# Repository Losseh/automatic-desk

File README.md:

# README

## Used components

### Microcontroller
Arduino Nano 328 SKU DFR0010 (from DFRobot)
[wiki](https://wiki.dfrobot.com/Arduino_Nano_328__SKU__DFR0010_)

### Current sensor
ACS712 5A

### Motor driver
[Cytron MD13S](https://www.cytron.io/p-13amp-6v-30v-dc-motor-driver)

### Motor
JGB37-555

# Troubleshooting

## Arduino-ide

### sandbox issue

```
[18644:1223/101056.126347:FATAL:setuid_sandbox_host.cc(158)] The SUID sandbox helper binary was found, but is not configured correctly. Rather than run without sandboxing I'm aborting now. You need to make sure that /home/justyna-halicz-szymanska/Programy/arduino-ide_2.3.7_Linux_64bit/chrome-sandbox is owned by root and has mode 4755.
Pułapka debuggera/breakpoint (zrzut pamięci)
```

solution
```
sudo chown root chrome-sandbox
sudo chmod g+x,u+s chrome-sandbox
```

### Error: programmer is not responding

trying to upload a program to dfrduino nano 4.0 using android ide. but getting:
```
Sketch uses 924 bytes (3%) of program storage space. Maximum is 30720 bytes.
Global variables use 9 bytes (0%) of dynamic memory, leaving 2039 bytes for local variables. Maximum is 2048 bytes.
Error: programmer is not responding Warning: attempt 1 of 10: not in sync: resp=0x00
Error: programmer is not responding Warning: attempt 2 of 10: not in sync: resp=0x00
Error: programmer is not responding Warning: attempt 3 of 10: not in sync: resp=0x00
...
```

solution
```
Select Arduino Nano
Try ATmega328P
If that doesn't work, try ATmega328P (Old Bootloader)

The Nano 4.0 is based on the ATmega328P, and the bootloader variant matters.
```

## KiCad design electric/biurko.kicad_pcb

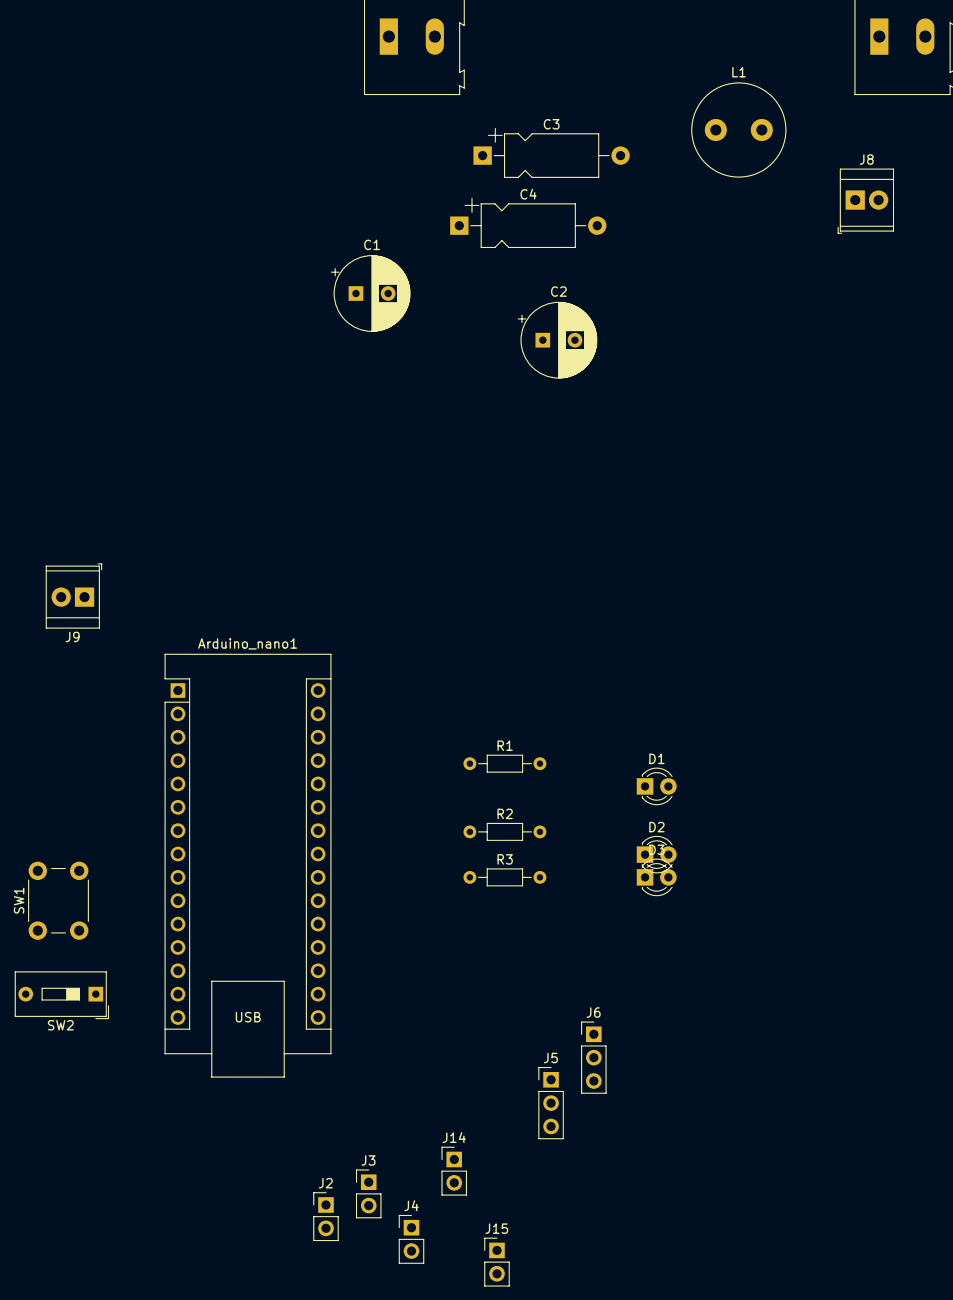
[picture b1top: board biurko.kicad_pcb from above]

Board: 2 copper layers, 25 parts (0 on the bottom side), 21 nets, no tracks yet.

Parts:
Arduino_nano1: Arduino_Nano
C1, C2: 470uF; CP_Radial_D8.0mm_P3.50mm
C3, C4: 100nF; CP_Axial_L10.0mm_D4.5mm_P15.00mm_Horizontal
D1: green; LED_D3.0mm
D2: red; LED_D3.0mm
D3: yellow; LED_D3.0mm
J1: 12V input screw terminal; TerminalBlock_Altech_AK300-2_P5.00mm
J2, J15: upper limit; PinHeader_1x02_P2.54mm_Vertical
J3, J14: lower limit; PinHeader_1x02_P2.54mm_Vertical
J4: encoder; PinHeader_1x02_P2.54mm_Vertical
J5: outer control; PinHeader_1x03_P2.54mm_Vertical
J6: motor control; PinHeader_1x03_P2.54mm_Vertical
J7: 12V motors screw terminal; TerminalBlock_Altech_AK300-2_P5.00mm
J8: 12V logic screw terminal; TerminalBlock_TE_282834-2_1x02_P2.54mm_Horizontal
J9: power input; TerminalBlock_TE_282834-2_1x02_P2.54mm_Horizontal
L1: 10uH; L_Radial_D10.0mm_P5.00mm_Neosid_SD12_style3
R1, R2, R3: 220R; R_Axial_DIN0204_L3.6mm_D1.6mm_P7.62mm_Horizontal
SW1: callibrate; SW_PUSH_6mm
SW2: debug; SW_DIP_SPSTx01_Slide_9.78x4.72mm_W7.62mm_P2.54mm

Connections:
+5VL: Arduino_nano1.4 (5V), R1.1, R2.1, R3.1
+7.5V: Arduino_nano1.1 (VIN), J9.1
+12L: C2.1, C4.1, J8.2, L1.2
+12P: C1.1, C3.1, J1.2, J7.2, L1.1
/callibrate_trg: Arduino_nano1.11 (D8), SW1.2
/callibrated: Arduino_nano1.10 (D7), D1.1 (K)
/debug: Arduino_nano1.15 (D13/SCK), SW2.1 (A)
/down: Arduino_nano1.7 (D4), J5.2
/encoder_out: Arduino_nano1.5 (D2/INT0), J4.1
/error: Arduino_nano1.9 (D6), D2.1 (K)
/lower_lmt: Arduino_nano1.13 (D10), J3.1, J15.1
/pwm: Arduino_nano1.14 (D11/MOSI), J6.2
/status: Arduino_nano1.8 (D5), D3.1 (K)
/up: Arduino_nano1.6 (D3/INT1), J5.1
/upper_lmt: Arduino_nano1.12 (D9), J2.1, J14.1
GND: Arduino_nano1.2 (GND), J2.2, J3.2, J4.2, J5.3, J6.3, J9.2, J14.2, J15.2, SW1.1, SW2.2 (B)
GND1: C1.2, C3.2, J7.1
unnamed: D1.2 (A), R1.2
unnamed: D2.2 (A), R2.2
unnamed: D3.2 (A), R3.2
unnamed: C2.2, C4.2, J8.1

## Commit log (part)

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2025-12-23 readme extension
